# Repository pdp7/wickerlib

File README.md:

# wickerlib
Collection of open source parts, circuits, and templates for KiCad.

Wickerlib is part of my quest to build my small hardware design business and turn around projects as quickly and with as little uncertainty as possible. As part of that process, I'm writing everything down and making my templates, libraries, workflow, reference circuits, and scripts publicly available.   

### Libraries

- wickerlib.dcm
- wickerlib.lib
- Wickerlib.pretty

### Templates

_Blank 2-layer and 4-layer OSH Park Templates_

- <a href="https://github.com/wickerbox/wickerlib/tree/master/templates/oshpark-2layer">OSH Park 2 Layer Generic</a>
- <a href="https://github.com/wickerbox/wickerlib/tree/master/templates/oshpark-4layer">OSH Park 4 Layer Generic</a>

_Project Templates_

- <a href="https://github.com/wickerbox/wickerlib/tree/master/templates/teensy-lc">Teensy LC Footprint</a>
- <a href="https://github.com/wickerbox/wickerlib/tree/master/templates/teensy-3.2">Teensy 3.2 Footprint</a>
- <a href="https://github.com/wickerbox/wickerlib/tree/master/templates/arduino-101-shield">Arduino 101 Shield</a>
- <a href="https://github.com/wickerbox/wickerlib/tree/master/templates/chip-dip-2layer">CHIP DIP Shield</a>
- <a href="https://github.com/wickerbox/wickerlib/tree/master/templates/atmega328">Atmega328 Project</a>
- <a href="https://github.com/wickerbox/wickerlib/tree/master/templates/atmega2560">Atmega2560 Project</a>

### Articles

1. KiCad Templates simplify starting a new project. 
1. Wickerlib Symbol and Footprint Library Management
1. Maintaining an Inventory
1. First Schematic and Editing Components 
1. Netlist and Footprint Association
1. Generating Bills of Material
1. Pre-fabrication Checklist
1. KiCad Board Layers
1. First Board and Editing Footprints
1. Generate Gerbers
1. Generate Paste Layers for Stencils
1. Generate Assembly Diagrams
1. Makefile Magic
1. Order from Digikey
1. Assembling the Boards
1. Tips for Testing and Bringing up Boards

### Scripts

- Create a BOM
- Generate gerbers
- Generate paste layers for a stencil
- Generate assembly files

### Circuits

Breadboard-compatible, proven, using wickerlib parts, with bills of material.

- Input Power Board (9V -> 5V -> 3.3V)

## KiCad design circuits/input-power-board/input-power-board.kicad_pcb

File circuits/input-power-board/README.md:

# Input Power Board

Breadboard-compatible board breaks out 9V, 5V, and 3.3V from a 9V battery.

### Bill of Materials

|Ref|Qty|Description|MF_Name|MF_PN|Digikey PN|
|---|---|-----------|-------|-----|----------|
|C1|1|CAP CER 0.1UF 50V C0G RADIAL|TDK FK26C0G1H104J|445-8532-ND|
|C2|1|CAP CER 10UF 25V X7R RADIAL|TDK FK16X7R1E106K|445-8351-ND|
|J1-J4|4|HEADER MALE 2POS TH 1x02 0.1"|Harwin|M20-9990246|952-2262-ND|
|J1A-J4A|4|CONN TERM SCREW GREEN 2.54MM 2POS TH|OnShoreTech|OSTVN02A150|ED10561-ND|
|J5|1|CONN PWR JACK 2.0X6.5MM HIGH CUR|Panasonic|PJ-202AH|CP-202AH-ND|
|U1|1|IC REG LDO 5V 1A NCP7805 TO220AB|ON Semi|NCP7805TG|NCP7805TGOS-ND|
|U2|1|IC REG LDO 3.3V 1A LD1117 TO220AB|STM|LD1117AV33|497-1485-5-ND|

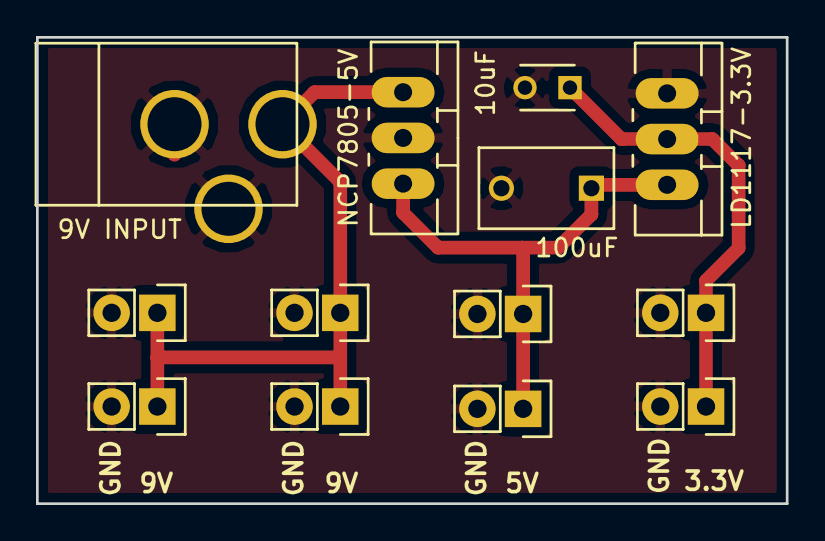
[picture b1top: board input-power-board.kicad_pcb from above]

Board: 2 copper layers, 41.7 x 25.9 mm, 13 parts (0 on the bottom side), 4 nets.

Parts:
9V INPUT: BARREL_JACK
10uF: 10uF; C_Disc_D3_P2.5
100uF: 100nF; C_Disc_D7.5_P5
J1, J2, J3, J4: HEADER; Pin_Header_Straight_1x02
J1A1, J2A1, J3A1, J4A1: SCREW; OSTVN02A150
LD1117-3.3V: LD1117-3.3V; TO-220_Neutral123_Vertical_LargePads
NCP7805-5V: NCP7805-5V; TO-220_Neutral123_Vertical_LargePads

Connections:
+3V3: 10uF.1, J4.1, J4A1.1, LD1117-3.3V.2
+5V: 100uF.1, J3.1, J3A1.1, LD1117-3.3V.3, NCP7805-5V.3
+9V: 9V INPUT.1, J1.1, J1A1.1, J2.1, J2A1.1, NCP7805-5V.1
GND: 9V INPUT.2, 9V INPUT.3, 10uF.2, 100uF.2, J1.2, J1A1.2, J2.2, J2A1.2, J3.2, J3A1.2, J4.2, J4A1.2, LD1117-3.3V.1, NCP7805-5V.2

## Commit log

2016-04-15 Added table of contents.
2016-04-15 Add reference inventory.csv file before sanitizing.
2016-04-16 Create LibraryPart class with attributes. Read in CSV, create list of parts.
2016-04-16 Don't read in lines where reference is empty, dash, or title line.
2016-04-16 Got a sorted list of 131 symbols to create in wickerlib.
2016-04-16 Able to create lib and dcm, open it in test project.
2016-04-21 Figured out field names! Wickerlib is done except for symbols.
2016-04-21 Changing how the names and values are set up in inventory to make wickerlib generation easier.
2016-04-24 Headersymbols.py file has all the symbols I could find.
2016-04-24 Finished wickerlib.lib and wickerlib.dcm.
2016-05-01 Added Arduino 101 template.
2016-05-01 Added wickerlib symbols and footprints. It's complete, with some placeholders. Needs editing.
2016-05-03 Added battery strap to library.
2016-05-03 Added complete Arduino 101 template with wickerlib features. Ready for use.
2016-05-03 Renamed it 101 shield.
2016-05-05 Added Atmega16U2 reference circuit schematic. Added lots of lib stuff.
2016-05-06 Okay we've created wickerlib. Now, BOM creation.
2016-05-06 Schematic verified, printed.
2016-05-06 Schematic PDF created. Exported rough BOM.
2016-05-06 Updated documentation.
2016-05-06 Added QFN32 package to lib.
2016-05-06 Wrestling with the KiCadBomExport script. It's really good!
2016-05-07 Added OSH Park 2 layer template.
2016-05-07 Added four layer OSH Park template.
2016-05-07 Adding README explaining structure of reference circuits.
2016-05-07 Updated path for wickerlib.
2016-05-07 Templates might be good.
2016-05-07 Tweaked Page Settings.
2016-05-07 Added explanation.
2016-05-07 Cleaned PFET symbol.
2016-05-08 Added DIP schematic and chip-dips lib. Updated wickerlib.
2016-05-08 The protoboard DIP project is complete.
2016-05-08 Final release of CHIP DIP blank and CHIP DIP Protoboard.
2016-05-10 Converted input power board to wickerlib and added it.
2016-05-10 New packages to wickerlib, fixed volt regs.
2016-05-10 Typo.
2016-05-10 Markdown tables are the worst.
2016-05-14 Added DIP Protoboard, DIP template, relay control board.
2016-05-14 Moved DIP Protoboard for CHIP to its own repo. Updated CHIP-DIP library.
2016-05-14 Added DIP template for CHIP.
2016-05-14 Added link to CHIP DIP template zip file.
2016-05-14 Tweaked the folder organization.
2016-05-14 Added README to libraries section.
2016-05-14 Added usage instructions for OSH Park templates, with links to template zip files.
2016-05-14 Forgot .zip.
2016-05-14 Removed development work from master.
2016-05-14 Clarified description of Wickerlib.
2016-05-14 Moved reference-circuits to circuits.
2016-05-14 Add minimum web, thickness, etc to templates.
2016-05-14 Removed cruft.
2016-05-14 Added Teensy LC and 3.2 lib symbols. Added schematics for both.
2016-05-14 Added Teensy LC bare template and test board.
2016-05-14 Ordered board. Updated README.
2016-05-14 Both Teensy templates are finished. Added Teensy footprint, tweaked symbol.
2016-05-14 Set default text size settings for all templates.
2016-05-14 Updated to reflect the recent templates.
2016-05-24 Updated input power board v1.1 and library.
2016-05-27 Update to symbol lib.
2016-05-27 Converted OSH Park 2l and 4l templates to actual KiCad templates.
2016-05-28 All templates have logo, info page.
2016-05-28 Zipped Wickerlib.pretty
2016-05-28 Added README with proper template instruction
2016-05-28 Simplified instructions.
2016-05-28 Another README tweak.
2016-05-28 Final README tweak.
2016-05-28 Releasing both OSH Park templates.
2016-05-28 Made the Teensy LC template independent.
2016-05-28 Clarified README. Added template zip.
2016-05-28 Took the README out.
2016-05-28 Releasing Teensy 3.2 template.
2016-05-28 Releasing the CHIP DIP template.
2016-05-28 Releasing Arduino 101 template.
2016-05-28 Tweaked readmes.
2016-06-24 Added bare Atmega328 and Atmega2560 project templates. Need circuits.
2016-07-13 Added heartbeat LED to Atmega2560 project.
2016-07-13 Added footprints and parts for LCD, keypad, reflow monitor boards.
2016-07-13 Finished Atmega328 template, including board layout.
2016-07-13 Updated README. Added Teensy LC template.
2016-07-13 Updated Atmega328 symbol.
2016-07-13 Added 328 and 2560 to readme.
2016-07-13 Added zip files.
2016-07-13 Ordered board, had to generate new gerbers.
2016-07-23 Wickerlib.Pretty has new names. Still needs actual footprint cleanup.
2016-07-23 Just about to prepend comments.
2016-07-23 All footprints now have header comments.
2016-08-13 Removed implementation and left only the raw template.
2016-08-30 Updated footprints. Removed circuits to breakout repo.
2016-10-11 Adjusted Wickerbox-specific templates.
2016-10-11 Updated default text sizes in templates.
2016-10-13 Added paste clearance setting.
2016-10-13 Added fiducial.
2016-10-13 Release.
2016-10-13 Update and release Arduino 101 shield template.
2016-10-13 Updated release zips for OSH Park templates.
2016-10-13 All templates are updated, new zips are released.
2016-10-13 Updated template links.
2016-10-13 Formatting!
2016-10-13 Clarified instructions.
2016-10-13 Added template links.
2016-10-29 Started script.
2016-10-29 F_Cu vals are integer layer numbers.
2016-10-29 Added plotting for all used layers, including inner layers.
2016-10-29 Aux grid has to be zero to get PDFs to come out. Why?
2016-10-29 All gerbers out. Need to create zip files.
2016-10-29 Now creates zip files for OSH Park and OSH Stencils.
2016-10-29 Added TODOs in header.
2016-10-29 If the gerber dir doesn't exist, create it.
2016-10-29 Added argparse. Added version and name inputs.
2016-10-29 Added list of footprints with verified status.
2016-10-29 Moved script to where it belongs.
2016-10-29 Fixed weird filename problem.
2016-10-30 Adjusted assembly diagram markings on all existing parts.
2016-10-30 Added Verified and Finished tags to footprints.
2016-10-30 Updated footprint list with new Finished category.
2016-10-30 Script now outputs README with Verify and Finish columns.
2016-10-30 Removed cruft. Updated Wickerlib.pretty zip.
2016-11-22 Made change to lib, also added BOM creation.
2016-11-23 Creates BOM, preview image, README, and final PDF.
2016-11-24 Removed non-UTF8 char from crystal symbol.
2016-11-24 Removed Verified and Package fields. Moved Description to Field 4.
2016-11-24 Updated wickerlib symbols up to BJTs, which have problems.
2016-11-25 Updating the wickerlib symbol libs. In middle of ICs.
2016-11-25 No more filled in symbol boxes.
2016-11-27 Fixed some cap and res packages.
2016-11-27 Fixed up trimpots.
2016-11-27 All Teensies are up to date.
2016-11-27 Forgot about the Teensy LC.
2016-11-27 All resistor symbols are cleaned up.
2016-11-27 Switches are cleaned up.
2016-11-27 Removed obsolete part.
2016-11-27 Removed obsolete part for real this time.
2016-11-27 Fixed up the MIC parts.
2016-11-28 LCDs and LEDs are updated.
2016-11-28 Updated keypad, lamp.
2016-12-03 Added FH34SRJ-34S-0.5SH symbol and footprint.
2016-12-03 Updated verified list.
2016-12-06 Gave up, started parsing .net file directly for BOM.
2016-12-06 Massive refactoring in prep for merging netlist parsing.
2016-12-06 working on bom. added e202 lib parts.
2016-12-06 Add flag -s to allow program to run on netlist without board file.
2016-12-09 Now create a master bom csv based on netlist.
2016-12-09 Add dynamic fields to the bom, nothing hard coded.
2016-12-09 Creates PDF, dynamic-size assembly and previews, and vendor CSV.
2016-12-09 Better errors. Puts bom files in bom/
2016-12-09 Create README with netlist project info.
2016-12-09 Created parts.
2016-12-12 Added E202 parts.
2016-12-13 Developed LaTeX template for PDF project outputs.
2016-12-16 Added testing dirs. Added kingfisher basic plot.
2016-12-16 Adjust plot_gerbers_and_drills function.
2016-12-16 Fixed up board_size function.
2016-12-17 Added function to create new project.
2016-12-17 Create new project works with new arg parsing.
2016-12-17 Create board outlines part of script good.
2016-12-18 Creates PDF from proj.json file.
2016-12-18 Able to create BOM and zip files. Added -v flag.
2016-12-18 Totally passing first tests
2016-12-18 Functional for both wickerbox and test client project.
2016-12-18 Major directory cleanup.
2016-12-18 Removed zips. Moved subdirs.
2016-12-19 When author not in proj.json, ignore its absence.
2016-12-19 Fix other spot where author not explicit referenced.
2016-12-19 Improved board preview images.
2016-12-19 Create final release zip file.
2016-12-19 remove dir.
2016-12-20 Major comment fixes.
2016-12-20 Added header and license info.
2016-12-24 Continue footprint cleanup.
2016-12-24 Update footprint status list.
2016-12-24 Added pcbnew.py here for the moment so I can find it.
2016-12-25 Finished a pass through cleaning footprints.
2016-12-25 Deleted 101 shield, fixed Uno shields.
2016-12-25 Check if list is done.
2016-12-25 Fixed or deleted breakout modules.
2016-12-25 Really need to hook this script.
2016-12-28 Update verified part list.
2016-12-31 Add version string to filenames.
2016-12-31 Add orientation mark. Create custom Atmega328 symbol.
2017-01-01 Updated template.
2017-01-01 Added box around resistor as a test.
2017-01-10 Add parts, add pin 1 marks.
2017-01-10 Added center hole.
2017-01-10 Created BK916, BK917.
2017-01-13 Create PDF with "v" in the filename.
2017-01-13 Create zip files with "v" in the filename.
2017-01-13 Create bom files with "v" in the filename.
2017-01-13 Added another stray version v.
2017-01-13 proj.json should only have version in format "1.0" not "v1.0"
2017-02-11 Footprint fixes. WIckerlib width= adjustment.
2017-02-11 Created KF config. Adjust README. Fix creation logic.
2017-02-11 update_version() updates .kicad_pcb and .sch
2017-02-11 Clear BOM dir when generating new BOMs.
2017-02-11 BOM now shows non-Digikey vendors.
2017-02-12 Supports width input args for PNGs in PDF.
2017-02-12 BOM and MFR file creation are independent.
2017-02-12 Include generic readable BOM CSV in release zip.
2017-02-12 Prioritize widths from json over args over default.
2017-02-12 Change function name to create_mfr_zip_files
2017-02-12 Create FabNotes file and rename Assembly files.
2017-02-12 Gerbers now subtract mask from silk.
2017-02-13 Fixed BOM S1/MF Name matching.
2017-04-02 Added blank Throwie layers example board.
2017-04-02 Updated libs.
2017-04-02 Finish Throwie example v1.0.
2017-04-05 Update.
2017-04-05 Created assy arg. Changed update_readme
2017-04-05 Seeed export ignores parts with no MF_PN.
2017-04-05 Creates assy.md file. Copies it to README
2017-04-06 Return error and exit if missing netlist.
2017-04-06 Assembly files function ready to merge pos and net.
2017-04-06 Converted netlist to json.
2017-04-06 Netlist parsed into legit json.
2017-04-06 Captured more netlist fields in json.
2017-04-06 Update BOMLine class.
2017-04-11 Build master, readable, Seeed BOMs from json.
2017-04-11 All output BOMs have netlist info. Need pos info.
2017-04-11 All SBA/Macrofab data in one list. Needs output files.
2017-04-11 Exports MacroFab .xyrs file with -a.
2017-04-11 Adjusted xyrs file to fit Macrofab upload.
2017-04-11 Creates assembly readme with SBA info.
2017-04-11 Produces a csv bom for Tempo Automation.
2017-07-20 Created basic ATMEGA328 breakout board

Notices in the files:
circuits/input-power-board/input-power-board.kicad_pcb:
Released under the CERN Open Hardware License v1.2
